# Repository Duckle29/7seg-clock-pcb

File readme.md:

### A small PCB for stacking on a WemosD1-mini to control two strips of WS2812 LEDs

This board has been made to work with [this](https://www.thingiverse.com/thing:2947883) 7 segment clock. It uses 2 mosfets as level-shifters instead of the levelshifter chip originally used. It also incorporates the barrel-jack into the PCB

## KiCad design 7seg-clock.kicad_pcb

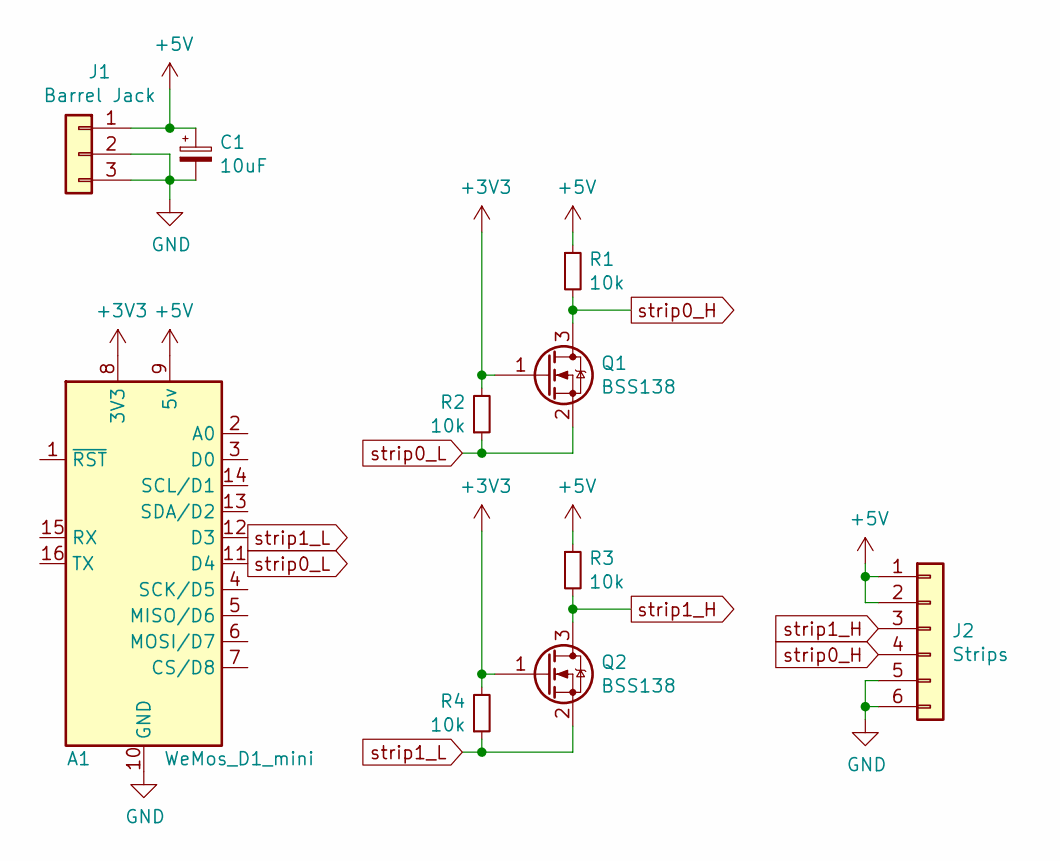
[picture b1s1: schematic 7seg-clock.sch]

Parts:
A1: WeMos_D1_mini
C1: 10uF; CP_Radial_D6.3mm_P2.50mm
J1: Barrel Jack; BarrelJack_Horizontal
J2: Strips; PinSocket_1x06_P2.54mm_Vertical
Q1, Q2: BSS138; SOT-23_Handsoldering
R1, R2, R3, R4: 10k; R_0603_1608Metric_Pad1.05x0.95mm_HandSolder

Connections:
+3V3: A1.8 (3V3), Q1.1 (G), Q2.1 (G), R2.2, R4.2
+5V: A1.9 (5v), C1.1, J1.1, J2.1, J2.2, R1.1, R3.1
GND: A1.10 (GND), C1.2, J1.2, J1.3, J2.5, J2.6
strip0_H: J2.4, Q1.3 (D), R1.2
strip0_L: A1.11 (D4), Q1.2 (S), R2.1
strip1_H: J2.3, Q2.3 (D), R3.2
strip1_L: A1.12 (D3), Q2.2 (S), R4.1

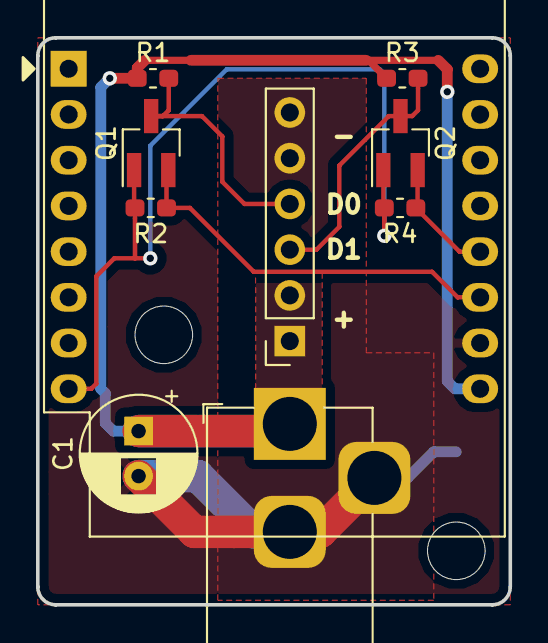
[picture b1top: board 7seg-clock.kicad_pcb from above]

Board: 2 copper layers, 26.2 x 31.5 mm, 10 parts (0 on the bottom side), 7 nets.

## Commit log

2018-07-04 Added images and readme
2018-07-04 Added PDF of schematic
2018-07-04 Moved docs and added 3D step file
2018-07-04 Added gerbers
2018-07-04 Closed kicad, PCBnew asked to save
2018-07-04 Changed barrel-jack footprint to use holes instead of slots
